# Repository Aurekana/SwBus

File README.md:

# Sweet Business Autorifle from Destiny 2

Presented as-is, your mileage may vary greatly. All these parts "should" work as they were used for a prototype and a second prototype, but those prototypes were fairly expensive. In the BOM I've attempted to add alternative sources or other options where applicable. Otherwise, modifications welcome and wanted, though if you use these files please attribute to me, see the LICENCE file (CC-BY-4.0). I worked hard on making these (~6 months).

Model modified from files found at Thingiverse by llkirikoull: https://www.thingiverse.com/thing:3837499

Assets also derived from files found at the Destiny STL Generator: http://www.destinystlgenerator.com/

Contents:
- 3D-STL = stl files for immediate 3D printing, have been proven on a Rostock Max v3.
- 3D-STEP = STEP files from CAD for editing purposes, some of which contain errors due to an iffy mesh export.
- PCB = Board and schematic files from EAGLECAD for PCB fabrication and modification, also the PCB BOM. 
- BOM = Bill of materials and part datasheets, documents, etc.
- Assembly = Assembly advice, assets, instructions, warnings, and related.

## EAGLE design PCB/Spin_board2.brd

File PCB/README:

# LED distribution board

Board and schematic files for the LED distribution board. 

Board purpose is to break out the signals from the slip-ring to the ten (10) barrels while avoiding a mess of wires that I'd been prone to end up with in prior projects. The board also incorporates signal resistors and power smoothing capacitors, and contains ten (10) handy connectors so that the building of the barrel assemblies can be done at a later stage.

This particular design uses a 1-wire Neopixel protocol as well as +5V and GND lines. Because I was space constrained I found some JST connectors that would fit, and since I needed to sent a lot of current (~1A) to each barrel and the wire gauge of the wire assemblies I found was so small (I hate making my own crimped wire assemblies), the +5V and GND are connected over two wires and the signal takes the middle wire.

To anyone reading this, a 3 or 4 pin connector would be a lot easier to connect and route so long as the wire gauge can handle ~1A per connector per +5V/GND line.

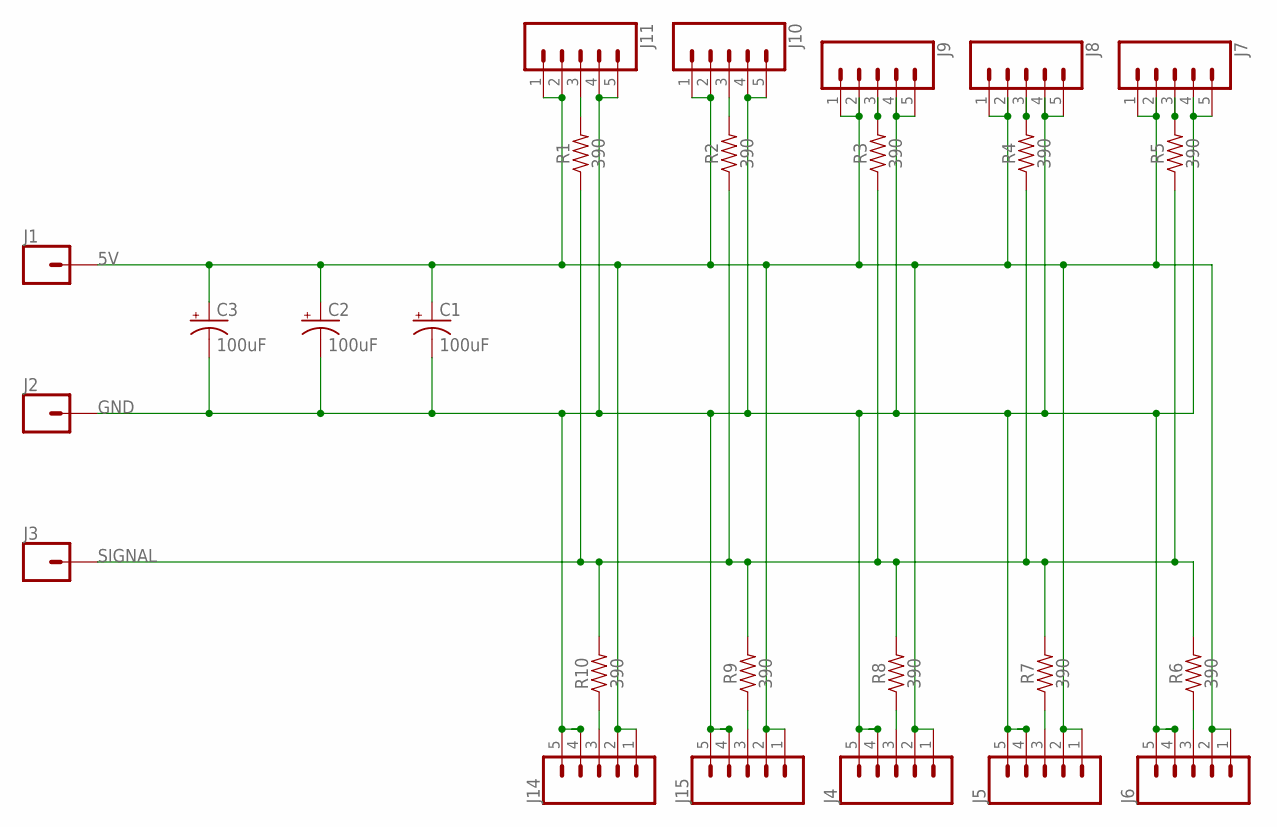
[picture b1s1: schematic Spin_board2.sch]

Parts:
C1, C2, C3: 100uF; CPOL-RADIAL-2.5MM-6.5MM
J1, J2, J3: CONN_01; 1X01
J4, J5, J6, J7, J8, J9, J10, J11, J14, J15: CONN_05SMD; 1X05_1MM
R1, R2, R3, R4, R5, R6, R7, R8, R9, R10: 390; 0603

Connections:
5V: C1.1 (+), C2.1 (+), C3.1 (+), J1.1, J4.1, J4.2, J5.1, J5.2, J6.1, J6.2, J7.1, J7.2, J8.1, J8.2, J9.1, J9.2, J10.1, J10.2, J11.1, J11.2, J14.1, J14.2, J15.1, J15.2
GND: C1.2 (-), C2.2 (-), C3.2 (-), J2.1, J4.4, J4.5, J5.4, J5.5, J6.4, J6.5, J7.4, J7.5, J8.4, J8.5, J9.4, J9.5, J10.4, J10.5, J11.4, J11.5, J14.4, J14.5, J15.4, J15.5
unnamed: J11.3, R1.2
unnamed: J10.3, R2.2
unnamed: J9.3, R3.2
unnamed: J8.3, R4.2
unnamed: J7.3, R5.2
unnamed: J6.3, R6.1
unnamed: J5.3, R7.1
unnamed: J4.3, R8.1
unnamed: J15.3, R9.1
unnamed: J14.3, R10.1
SIGNAL: J3.1, R1.1, R2.1, R3.1, R4.1, R5.1, R6.2, R7.2, R8.2, R9.2, R10.2

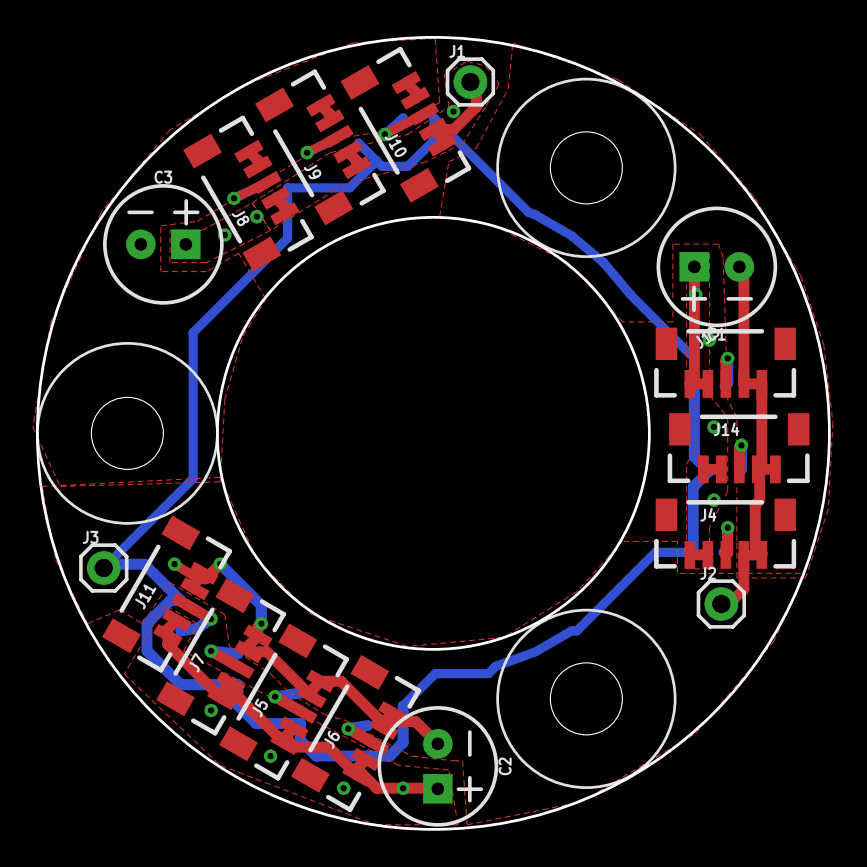
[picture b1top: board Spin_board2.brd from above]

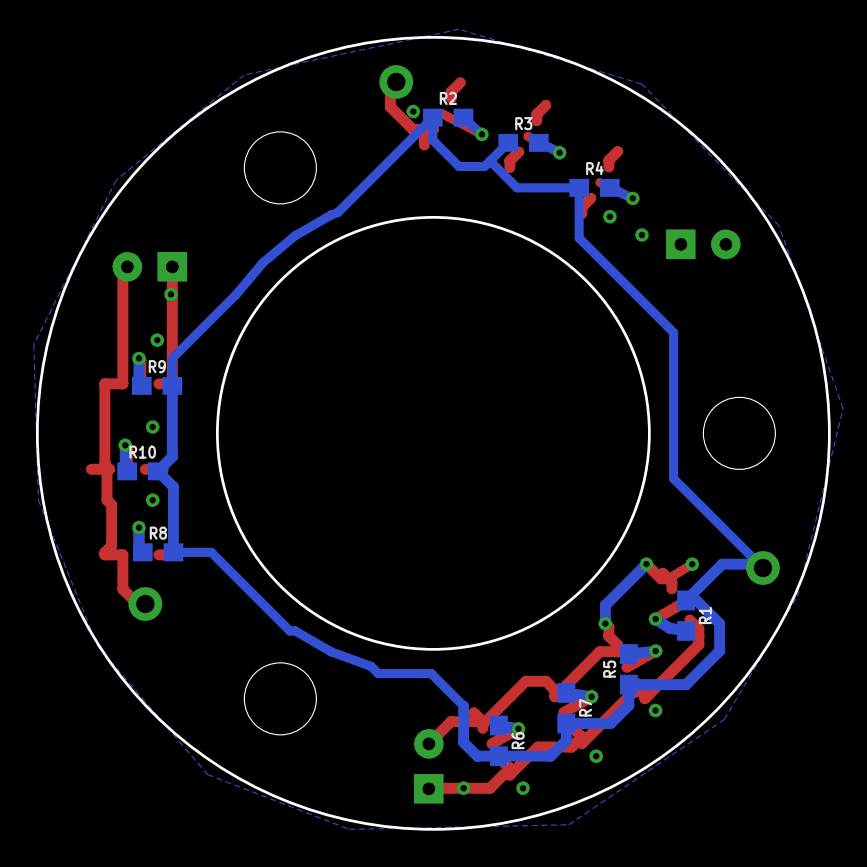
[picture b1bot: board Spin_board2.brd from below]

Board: 2 copper layers, 44.0 x 44.0 mm, 26 parts (10 on the bottom side), 13 nets.

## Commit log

2020-02-20 Initial release
    Initial draft of readme.md
2020-02-20 Formatting update
2020-02-20 Initial release
2020-02-20 Create PARTLIST
2020-02-20 Rename README to README.md
2020-02-20 v0.1
2020-02-20 CircuitPython main.py v1.0 for Trinket M0
2020-02-20 Pololu Motor Controller config file
2020-02-20 v0.2
2020-02-23 Updated to newest geometry
2020-02-23 Steps 001 to 005
2020-02-23 Steps 006 and 007 added
2020-02-23 Added Steps 008 and 009.
2020-02-23 Added Steps 010 and 011.
2020-02-23 Updated wire routing path
2020-02-23 Step Order Change
2020-02-23 Updated Step 011
2020-02-23 Updated Step 011 Title
2020-02-23 Updated step 011 wording to be more correct
2020-02-23 Added steps 012 and 013
2020-02-23 Updated verbage
2020-02-24 Added steps 014 and 015.
2020-02-24 Added Steps 016, 017, 018.
2020-02-24 Added steps 019 and 020
2020-02-24 Added 021 and 022.
2020-02-24 Added 023, 024, 025, 026, 027, and 028
2020-02-24 Updated BOM
2020-02-24 Added different formats.

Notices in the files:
parts and their libraries:
SparkFun-Capacitors: Licensing: Creative Commons ShareAlike 4.0 International - https://creativecommons.org/licenses/by-sa/4.0
